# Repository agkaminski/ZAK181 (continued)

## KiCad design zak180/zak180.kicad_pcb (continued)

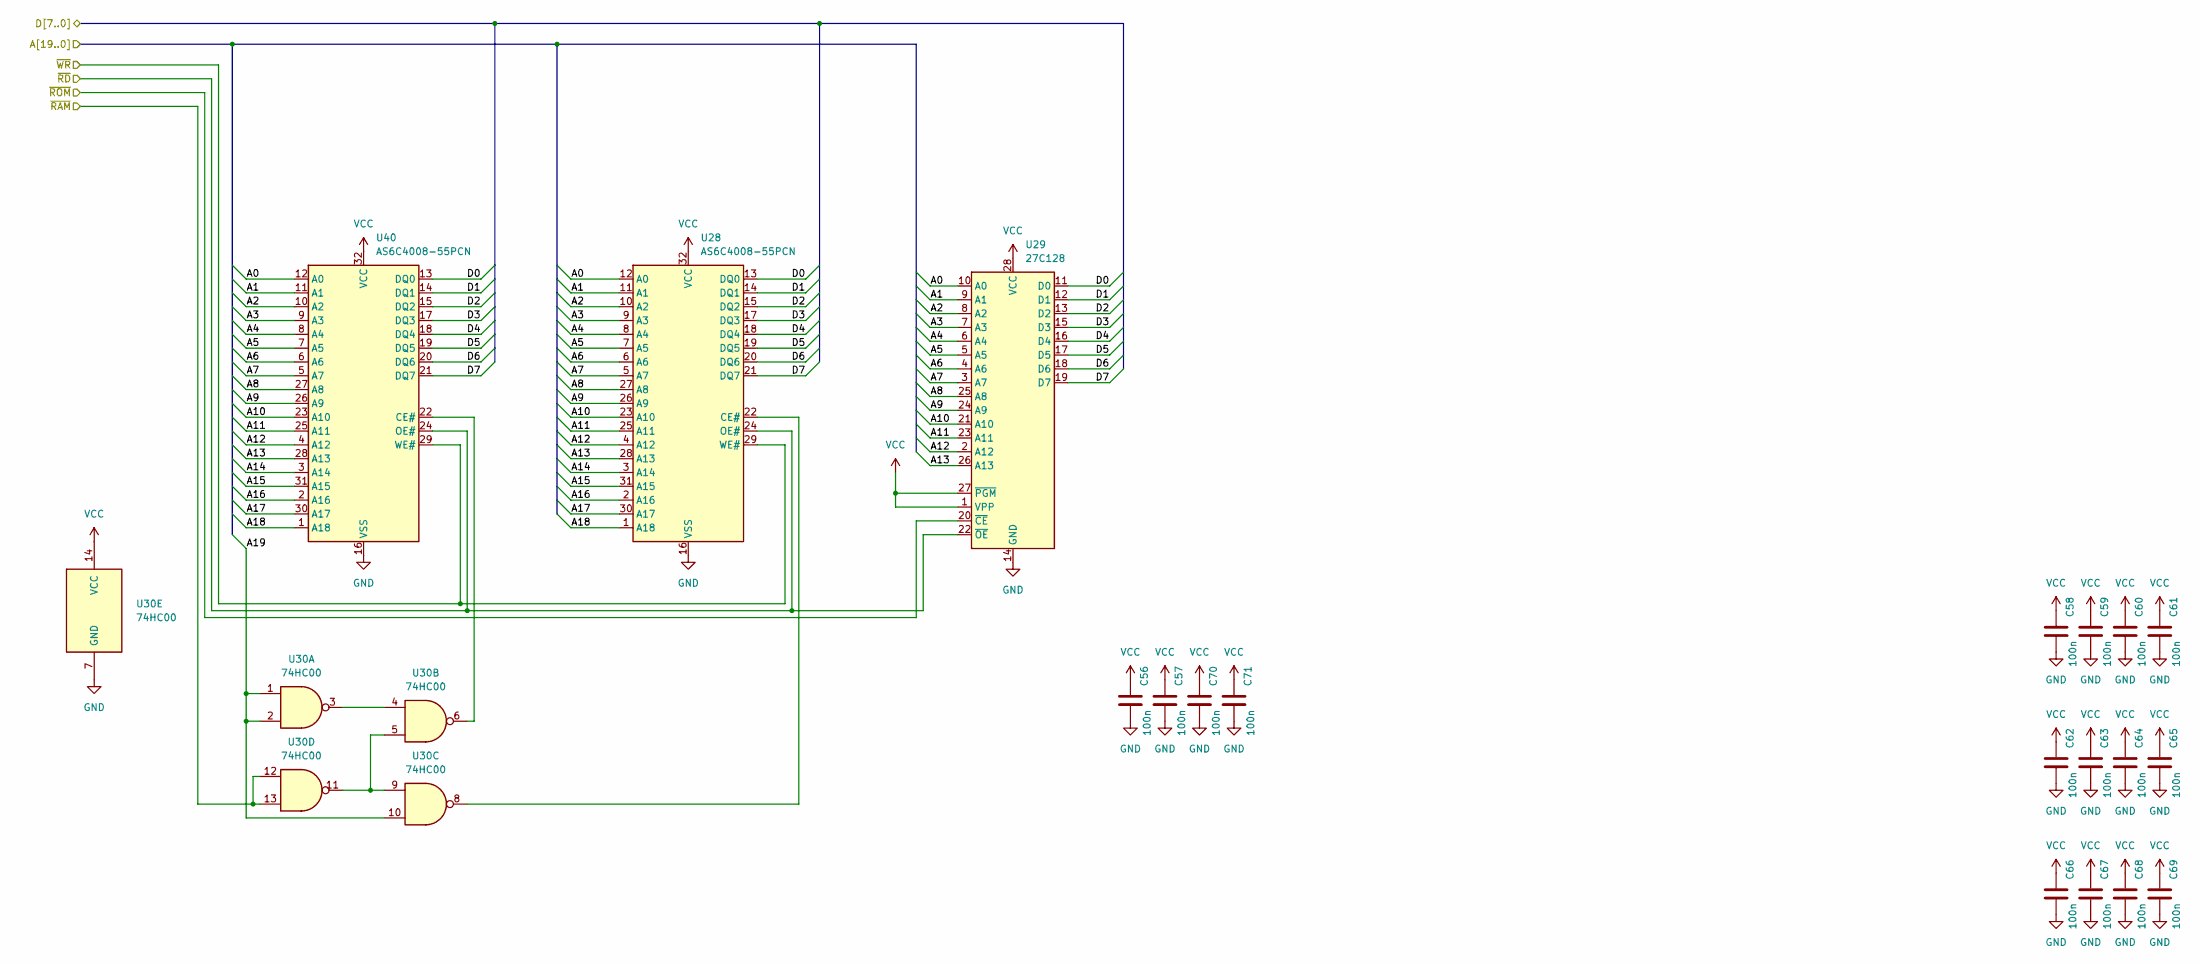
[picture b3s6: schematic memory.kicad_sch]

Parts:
C56, C57, C58, C59, C60, C61, C62, C63, C64, C65, C66, C67, C68, C69, C70, C71: 100n; C_Disc_D5.0mm_W2.5mm_P2.50mm
U28, U40: AS6C4008-55PCN; DIP-32_W15.24mm
U29: 27C128; DIP-28_W15.24mm
U30: 74HC00; DIP-14_W7.62mm

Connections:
/cpu/A0: U28.12 (A0), U29.10 (A0), U40.12 (A0); also elsewhere on the board
/cpu/A1: U28.11 (A1), U29.9 (A1), U40.11 (A1); also elsewhere on the board
/cpu/A2: U28.10 (A2), U29.8 (A2), U40.10 (A2); also elsewhere on the board
/cpu/A3: U28.9 (A3), U29.7 (A3), U40.9 (A3); also elsewhere on the board
/cpu/A4: U28.8 (A4), U29.6 (A4), U40.8 (A4); also elsewhere on the board
/cpu/A5: U28.7 (A5), U29.5 (A5), U40.7 (A5); also elsewhere on the board
/cpu/A6: U28.6 (A6), U29.4 (A6), U40.6 (A6); also elsewhere on the board
/cpu/A7: U28.5 (A7), U29.3 (A7), U40.5 (A7); also elsewhere on the board
/cpu/A8: U28.27 (A8), U29.25 (A8), U40.27 (A8); also elsewhere on the board
/cpu/A9: U28.26 (A9), U29.24 (A9), U40.26 (A9); also elsewhere on the board
/cpu/A10: U28.23 (A10), U29.21 (A10), U40.23 (A10); also elsewhere on the board
/cpu/A11: U28.25 (A11), U29.23 (A11), U40.25 (A11); also elsewhere on the board
/cpu/A12: U28.4 (A12), U29.2 (A12), U40.4 (A12); also elsewhere on the board
/cpu/A13: U28.28 (A13), U29.26 (A13), U40.28 (A13); also elsewhere on the board
/cpu/A14: U28.3 (A14), U40.3 (A14); also elsewhere on the board
/cpu/A15: U28.31 (A15), U40.31 (A15); also elsewhere on the board
/cpu/A16: U28.2 (A16), U40.2 (A16); also elsewhere on the board
/cpu/A17: U28.30 (A17), U40.30 (A17); also elsewhere on the board
/cpu/A18: U28.1 (A18), U40.1 (A18); also elsewhere on the board
/cpu/A19: U30.1, U30.2, U30.10; also elsewhere on the board
/cpu/D0: U28.13 (DQ0), U29.11 (D0), U40.13 (DQ0); also elsewhere on the board
/cpu/D1: U28.14 (DQ1), U29.12 (D1), U40.14 (DQ1); also elsewhere on the board
/cpu/D2: U28.15 (DQ2), U29.13 (D2), U40.15 (DQ2); also elsewhere on the board
/cpu/D3: U28.17 (DQ3), U29.15 (D3), U40.17 (DQ3); also elsewhere on the board
/cpu/D4: U28.18 (DQ4), U29.16 (D4), U40.18 (DQ4); also elsewhere on the board
/cpu/D5: U28.19 (DQ5), U29.17 (D5), U40.19 (DQ5); also elsewhere on the board
/cpu/D6: U28.20 (DQ6), U29.18 (D6), U40.20 (DQ6); also elsewhere on the board
/cpu/D7: U28.21 (DQ7), U29.19 (D7), U40.21 (DQ7); also elsewhere on the board
/cpu/~RAM: U30.12, U30.13; also elsewhere on the board
/cpu/~RD: U28.24 (OE#), U29.22 (~OE), U40.24 (OE#); also elsewhere on the board
/cpu/~ROM: U29.20 (~CE); also elsewhere on the board
/cpu/~WR: U28.29 (WE#), U40.29 (WE#); also elsewhere on the board
GND: C56.2, C57.2, C58.2, C59.2, C60.2, C61.2, C62.2, C63.2, C64.2, C65.2, C66.2, C67.2, C68.2, C69.2, C70.2, C71.2, U28.16 (VSS), U29.14 (GND), U30.7 (GND), U40.16 (VSS); also elsewhere on the board
unnamed: U28.22 (CE#), U30.8
unnamed: U30.3, U30.4
unnamed: U30.5, U30.9, U30.11
unnamed: U30.6, U40.22 (CE#)
VCC: C56.1, C57.1, C58.1, C59.1, C60.1, C61.1, C62.1, C63.1, C64.1, C65.1, C66.1, C67.1, C68.1, C69.1, C70.1, C71.1, U28.32 (VCC), U29.1 (VPP), U29.27 (~PGM), U29.28 (VCC), U30.14 (VCC), U40.32 (VCC); also elsewhere on the board

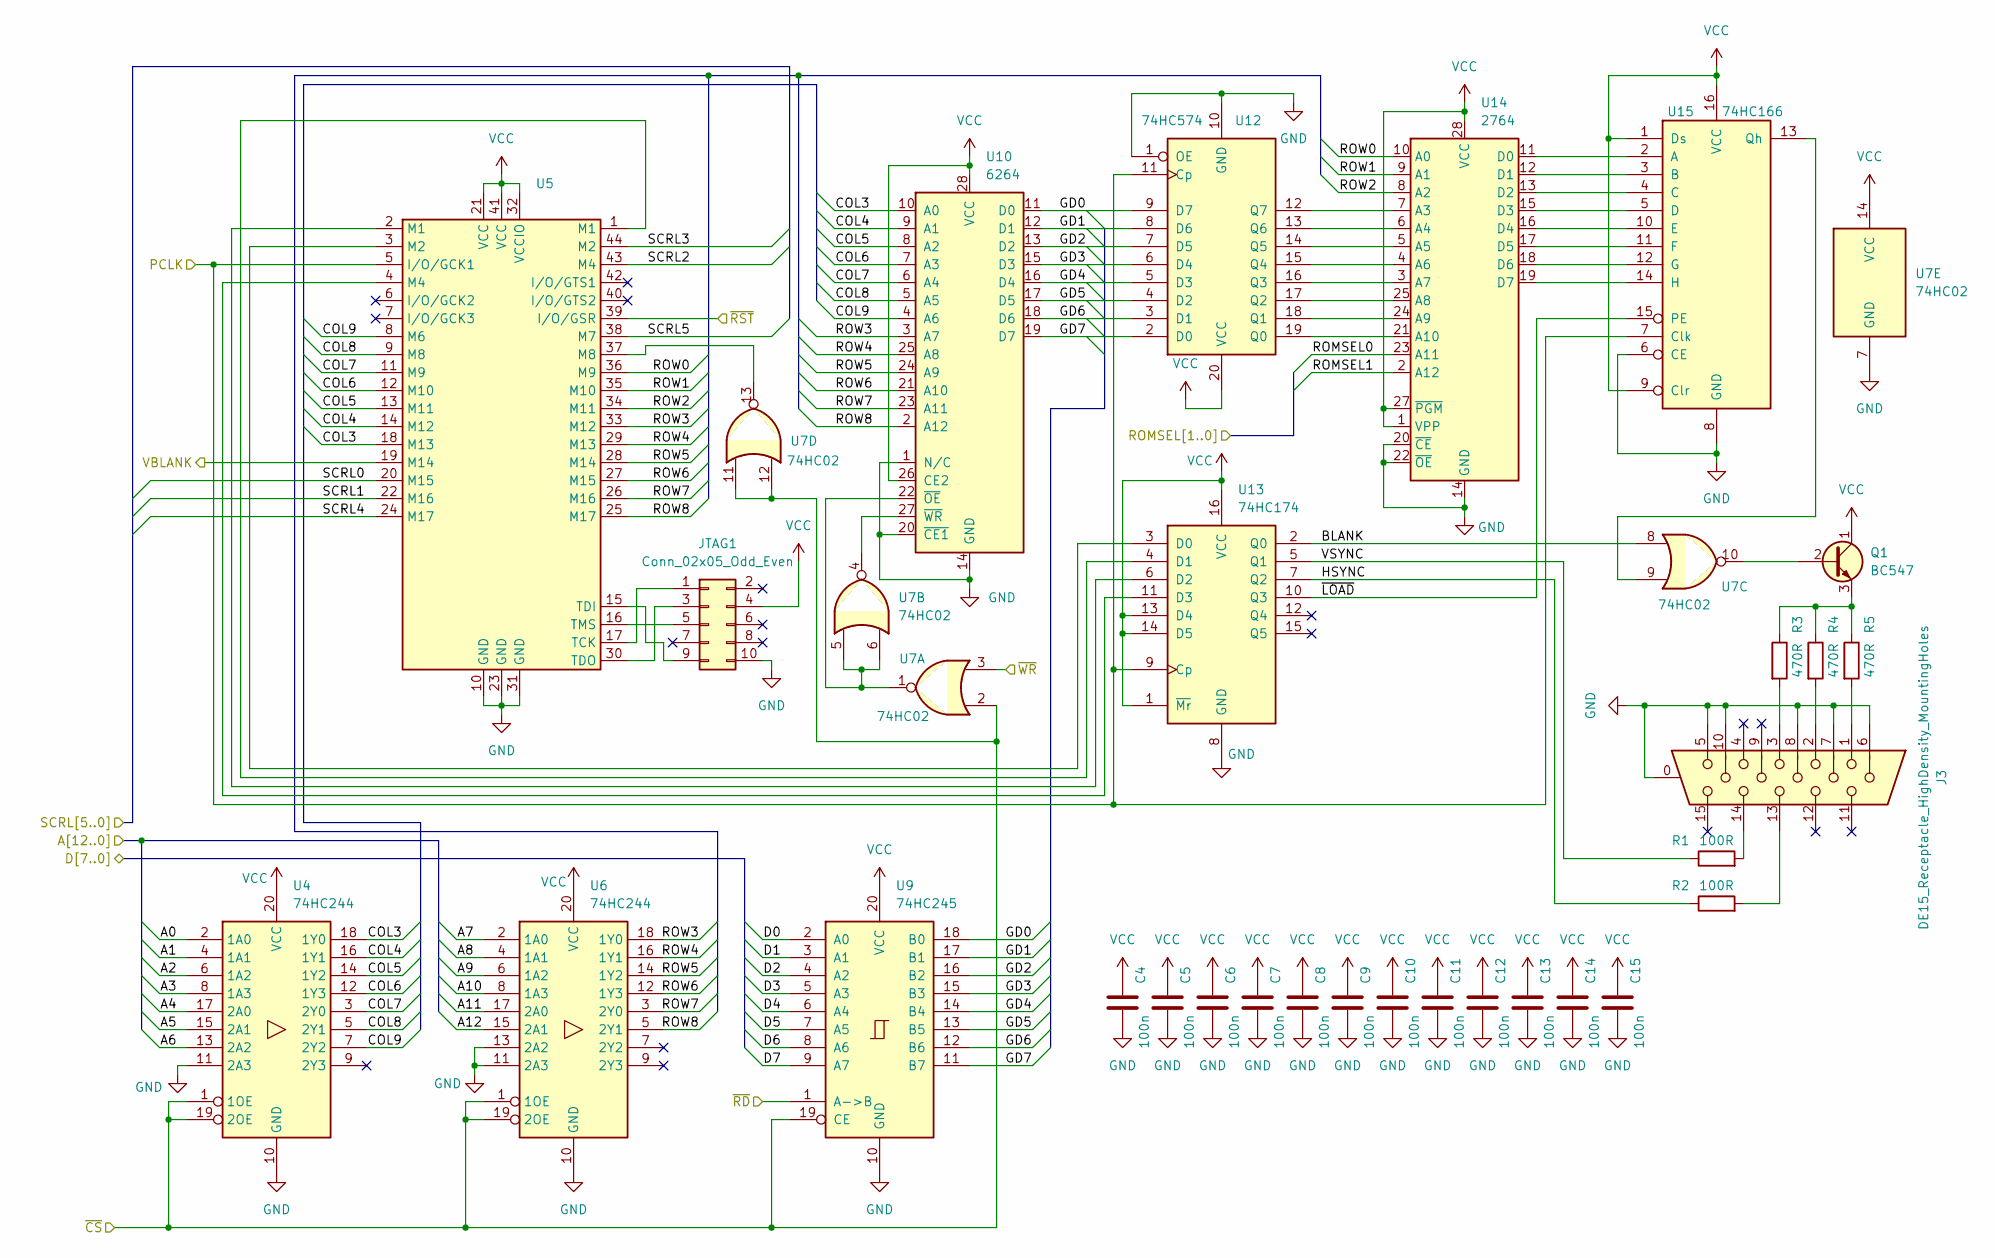
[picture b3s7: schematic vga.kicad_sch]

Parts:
C4, C5, C6, C7, C8, C9, C10, C11, C12, C13, C14, C15: 100n; C_Disc_D5.0mm_W2.5mm_P2.50mm
J3: DE15_Receptacle_HighDensity_MountingHoles; DSUB-15-HD_Female_Horizontal_P2.29x1.98mm_EdgePinOffset3.03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
JTAG1: Conn_02x05_Odd_Even; IDC-Header_2x05_P2.54mm_Vertical
Q1: BC547; TO-92
R1, R2: 100R; R_Axial_DIN0207_L6.3mm_D2.5mm_P7.62mm_Horizontal
R3, R4, R5: 470R; R_Axial_DIN0207_L6.3mm_D2.5mm_P7.62mm_Horizontal
U4: 74HC244; DIP-20_W7.62mm
U5: XC9536PC44; PLCC-44_THT-Socket
U6: 74HC244
U7: 74HC02; DIP-14_W7.62mm
U9: 74HC245; DIP-20_W7.62mm
U10: 6264; DIP-28_W15.24mm
U12: 74HC574; DIP-20_W7.62mm
U13: 74HC174; DIP-16_W7.62mm
U14: 2764; DIP-28_W15.24mm
U15: 74HC166; DIP-16_W7.62mm

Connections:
/clock/25.175 MHz: U5.5 (I/O/GCK1), U12.11 (Cp), U13.9 (Cp), U15.7 (Clk); also elsewhere on the board
/clock/~RST: U5.39 (I/O/GSR); also elsewhere on the board
/cpu/A0: U4.2 (1A0); also elsewhere on the board
/cpu/A1: U4.4 (1A1); also elsewhere on the board
/cpu/A2: U4.6 (1A2); also elsewhere on the board
/cpu/A3: U4.8 (1A3); also elsewhere on the board
/cpu/A4: U4.17 (2A0); also elsewhere on the board
/cpu/A5: U4.15 (2A1); also elsewhere on the board
/cpu/A6: U4.13 (2A2); also elsewhere on the board
/cpu/A7: U6.2 (1A0); also elsewhere on the board
/cpu/A8: U6.4 (1A1); also elsewhere on the board
/cpu/A9: U6.6 (1A2); also elsewhere on the board
/cpu/A10: U6.8 (1A3); also elsewhere on the board
/cpu/A11: U6.17 (2A0); also elsewhere on the board
/cpu/A12: U6.15 (2A1); also elsewhere on the board
/cpu/D0: U9.2 (A0); also elsewhere on the board
/cpu/D1: U9.3 (A1); also elsewhere on the board
/cpu/D2: U9.4 (A2); also elsewhere on the board
/cpu/D3: U9.5 (A3); also elsewhere on the board
/cpu/D4: U9.6 (A4); also elsewhere on the board
/cpu/D5: U9.7 (A5); also elsewhere on the board
/cpu/D6: U9.8 (A6); also elsewhere on the board
/cpu/D7: U9.9 (A7); also elsewhere on the board
/cpu/VBLANK: U5.19 (M14); also elsewhere on the board
/cpu/~RD: U9.1 (A->B); also elsewhere on the board
/cpu/~VRAM: U4.1 (1OE), U4.19 (2OE), U6.1 (1OE), U6.19 (2OE), U7.2, U7.11, U7.12, U9.19 (CE); also elsewhere on the board
/cpu/~WR: U7.3; also elsewhere on the board
/sound/ROMSEL0: U14.23 (A11); also elsewhere on the board
/sound/ROMSEL1: U14.2 (A12); also elsewhere on the board
/sound/SCRL0: U5.20 (M15); also elsewhere on the board
/sound/SCRL1: U5.22 (M16); also elsewhere on the board
/sound/SCRL2: U5.43 (M4); also elsewhere on the board
/sound/SCRL3: U5.44 (M2); also elsewhere on the board
/sound/SCRL4: U5.24 (M17); also elsewhere on the board
/sound/SCRL5: U5.38 (M7); also elsewhere on the board
/vga/BLANK: U7.8, U13.2 (Q0)
/vga/COL3: U4.18 (1Y0), U5.18 (M13), U10.10 (A0)
/vga/COL4: U4.16 (1Y1), U5.14 (M12), U10.9 (A1)
/vga/COL5: U4.14 (1Y2), U5.13 (M11), U10.8 (A2)
/vga/COL6: U4.12 (1Y3), U5.12 (M10), U10.7 (A3)
/vga/COL7: U4.3 (2Y0), U5.11 (M9), U10.6 (A4)
/vga/COL8: U4.5 (2Y1), U5.9 (M8), U10.5 (A5)
/vga/COL9: U4.7 (2Y2), U5.8 (M6), U10.4 (A6)
/vga/GD0: U9.18 (B0), U10.11 (D0), U12.9 (D7)
/vga/GD1: U9.17 (B1), U10.12 (D1), U12.8 (D6)
/vga/GD2: U9.16 (B2), U10.13 (D2), U12.7 (D5)
/vga/GD3: U9.15 (B3), U10.15 (D3), U12.6 (D4)
/vga/GD4: U9.14 (B4), U10.16 (D4), U12.5 (D3)
/vga/GD5: U9.13 (B5), U10.17 (D5), U12.4 (D2)
/vga/GD6: U9.12 (B6), U10.18 (D6), U12.3 (D1)
/vga/GD7: U9.11 (B7), U10.19 (D7), U12.2 (D0)
/vga/HSYNC: R2.1, U13.7 (Q2)
/vga/ROW0: U5.36 (M9), U14.10 (A0)
/vga/ROW1: U5.35 (M10), U14.9 (A1)
/vga/ROW2: U5.34 (M11), U14.8 (A2)
/vga/ROW3: U5.33 (M12), U6.18 (1Y0), U10.3 (A7)
/vga/ROW4: U5.29 (M13), U6.16 (1Y1), U10.25 (A8)
/vga/ROW5: U5.28 (M14), U6.14 (1Y2), U10.24 (A9)
/vga/ROW6: U5.27 (M15), U6.12 (1Y3), U10.21 (A10)
/vga/ROW7: U5.26 (M16), U6.3 (2Y0), U10.23 (A11)
/vga/ROW8: U5.25 (M17), U6.5 (2Y1), U10.2 (A12)
/vga/VSYNC: R1.1, U13.5 (Q1)
/vga/~LOAD: U13.10 (Q3), U15.15 (PE)
GND: C4.2, C5.2, C6.2, C7.2, C8.2, C9.2, C10.2, C11.2, C12.2, C13.2, C14.2, C15.2, J3.0, J3.5, J3.6, J3.7, J3.8, J3.10, JTAG1.10, U4.10 (GND), U4.11 (2A3), U5.10 (GND), U5.23 (GND), U5.31 (GND), U6.10 (GND), U6.11 (2A3), U6.13 (2A2), U7.7 (GND), U9.10 (GND), U10.1 (N/C), U10.14 (GND), U10.20 (~CE1), U12.1 (OE), U12.10 (GND), U13.8 (GND), U14.14 (GND), U14.20 (~CE), U14.22 (~OE), U15.6 (CE), U15.8 (GND); also elsewhere on the board
unnamed: J3.1, R5.2
unnamed: J3.2, R4.2
unnamed: J3.3, R3.2
unnamed: J3.13, R2.2
unnamed: J3.14, R1.2
unnamed: JTAG1.1, U5.17 (TCK)
unnamed: JTAG1.3, U5.30 (TDO)
unnamed: JTAG1.5, U5.16 (TMS)
unnamed: JTAG1.9, U5.15 (TDI)
unnamed: Q1.2 (B), U7.10
unnamed: Q1.3 (E), R3.1, R4.1, R5.1
unnamed: U5.37 (M8), U7.13
unnamed: U7.1, U7.5, U7.6, U10.22 (~OE)
unnamed: U7.4, U10.27 (~WR)
unnamed: U12.19 (Q0), U14.21 (A10)
unnamed: U12.18 (Q1), U14.24 (A9)
unnamed: U12.17 (Q2), U14.25 (A8)
unnamed: U12.16 (Q3), U14.3 (A7)
unnamed: U12.15 (Q4), U14.4 (A6)
unnamed: U12.14 (Q5), U14.5 (A5)
unnamed: U12.13 (Q6), U14.6 (A4)
unnamed: U12.12 (Q7), U14.7 (A3)
unnamed: U5.3 (M2), U13.3 (D0)
unnamed: U5.1 (M1), U13.4 (D1)
unnamed: U5.2 (M1), U13.6 (D2)
unnamed: U5.4 (M4), U13.11 (D3)
unnamed: U14.11 (D0), U15.2 (A)
unnamed: U14.12 (D1), U15.3 (B)
unnamed: U14.13 (D2), U15.4 (C)
unnamed: U14.15 (D3), U15.5 (D)
unnamed: U14.16 (D4), U15.10 (E)
unnamed: U14.17 (D5), U15.11 (F)
unnamed: U14.18 (D6), U15.12 (G)
unnamed: U14.19 (D7), U15.14 (H)
unnamed: U7.9, U15.13 (Qh)
VCC: C4.1, C5.1, C6.1, C7.1, C8.1, C9.1, C10.1, C11.1, C12.1, C13.1, C14.1, C15.1, JTAG1.4, Q1.1 (C), U4.20 (VCC), U5.21 (VCC), U5.32 (VCCIO), U5.41 (VCC), U6.20 (VCC), U7.14 (VCC), U9.20 (VCC), U10.26 (CE2), U10.28 (VCC), U12.20 (VCC), U13.1 (~Mr), U13.13 (D4), U13.14 (D5), U13.16 (VCC), U14.1 (VPP), U14.27 (~PGM), U14.28 (VCC), U15.1 (Ds), U15.9 (Clr), U15.16 (VCC); also elsewhere on the board

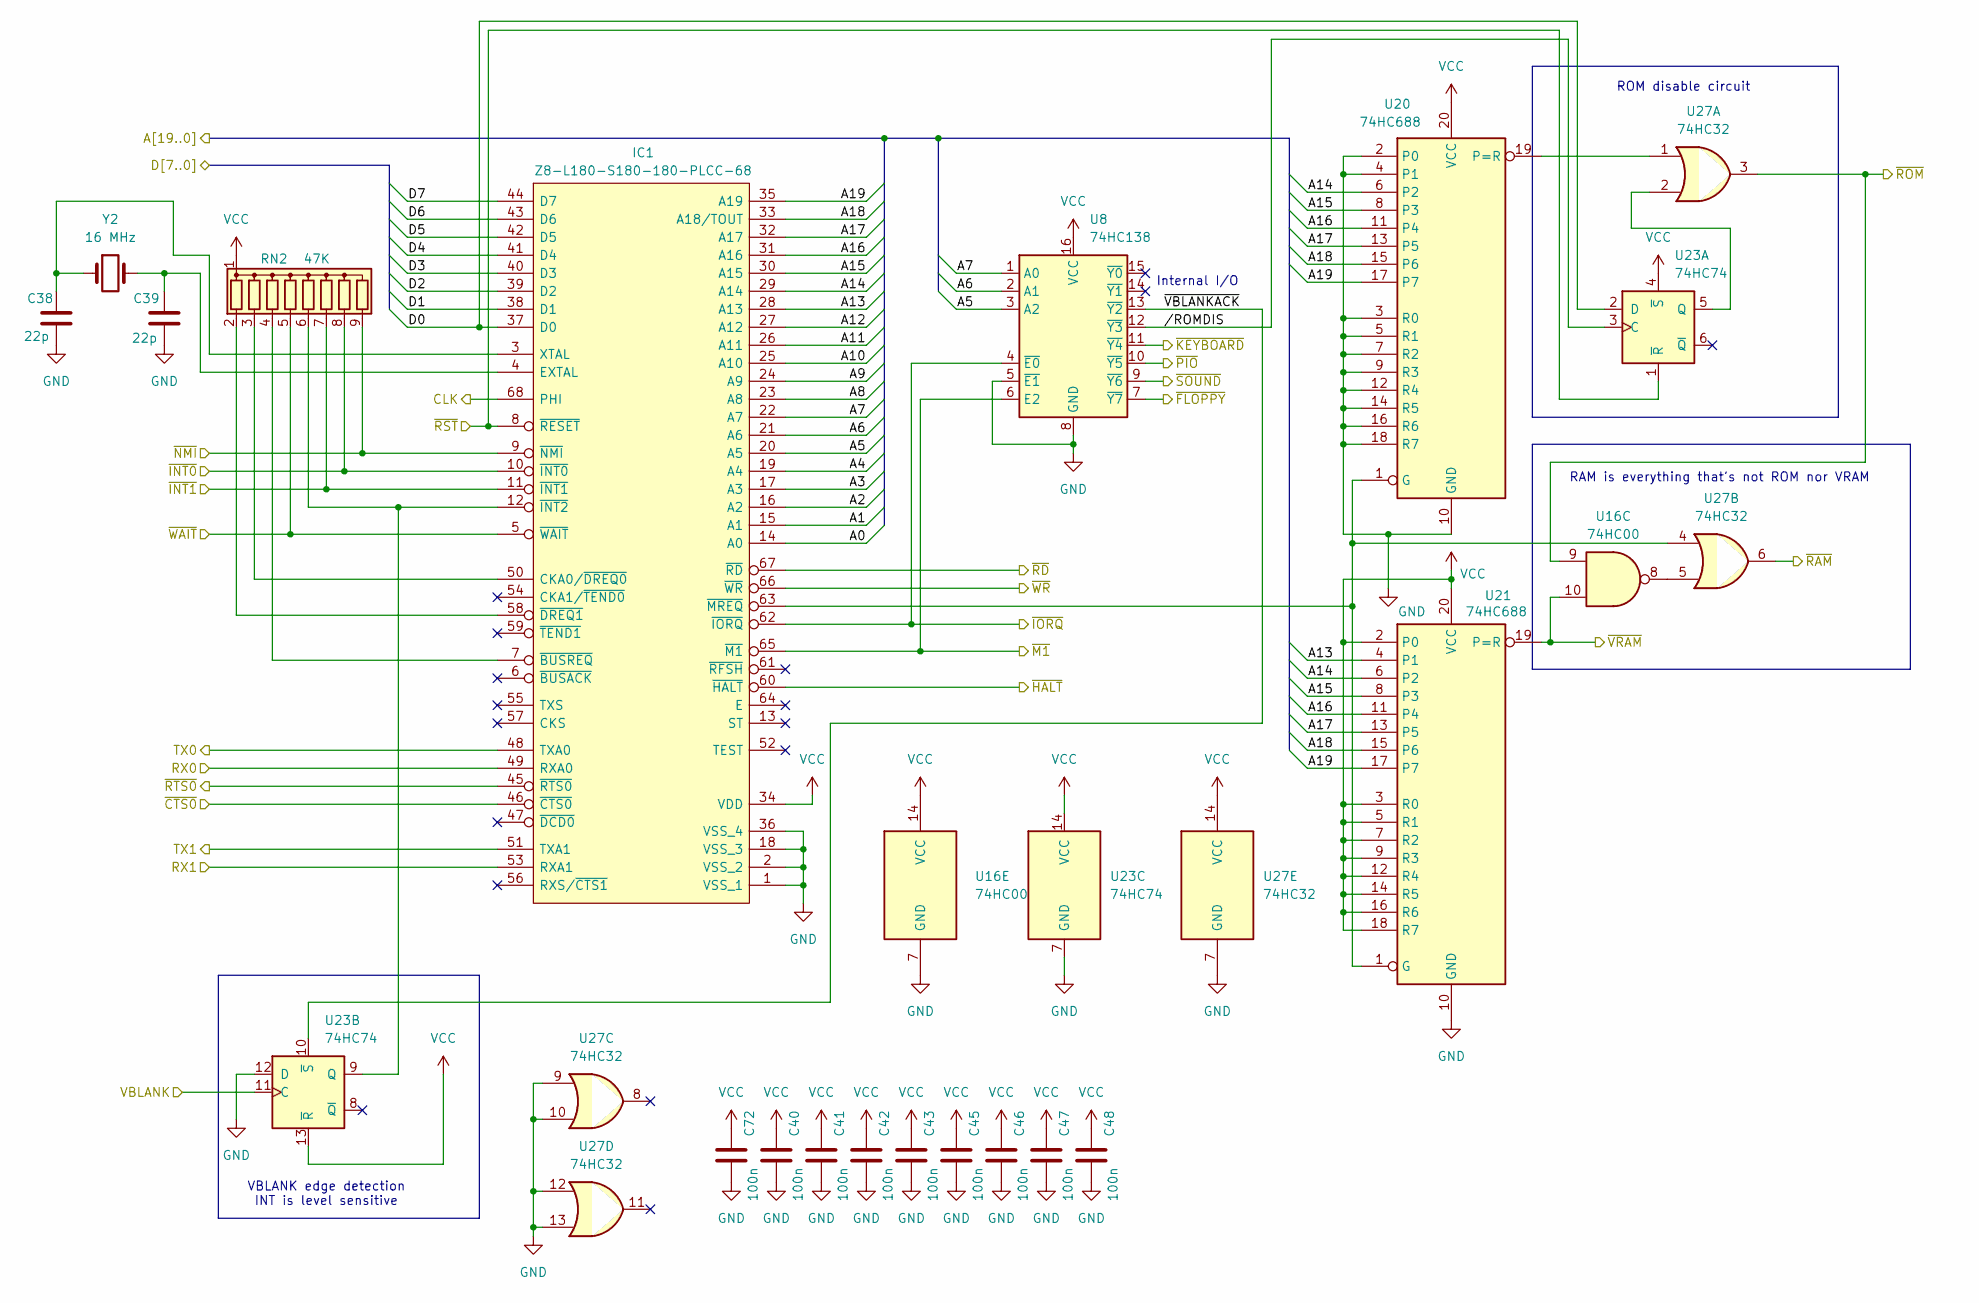
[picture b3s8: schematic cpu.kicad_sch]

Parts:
C38, C39: 22p; C_Disc_D4.3mm_W1.9mm_P5.00mm
C40, C41, C42, C43, C45, C46, C47, C48, C72: 100n; C_Disc_D5.0mm_W2.5mm_P2.50mm
IC1: Z8-L180-S180-180-PLCC-68; PLCC-68_THT-Socket; Manufacturer_Part_Number Z8S18033VSG; Mouser Part Number 692-Z8S18033VSG
RN2: 47K; R_Array_SIP9
U8: 74HC138; DIP-16_W7.62mm
U16: 74HC00; DIP-14_W7.62mm
U20, U21: 74HC688; DIP-20_W7.62mm
U23: 74HC74; DIP-14_W7.62mm
U27: 74HC32; DIP-14_W7.62mm
Y2: 16 MHz; Crystal_HC49-4H_Vertical

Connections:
/clock/~RST: IC1.8 (~RESET), U23.1 (~R); also elsewhere on the board
/cpu/A0: IC1.14 (A0); also elsewhere on the board
/cpu/A1: IC1.15 (A1); also elsewhere on the board
/cpu/A2: IC1.16 (A2); also elsewhere on the board
/cpu/A3: IC1.17 (A3); also elsewhere on the board
/cpu/A4: IC1.19 (A4); also elsewhere on the board
/cpu/A5: IC1.20 (A5), U8.3 (A2); also elsewhere on the board
/cpu/A6: IC1.21 (A6), U8.2 (A1); also elsewhere on the board
/cpu/A7: IC1.22 (A7), U8.1 (A0); also elsewhere on the board
/cpu/A8: IC1.23 (A8); also elsewhere on the board
/cpu/A9: IC1.24 (A9); also elsewhere on the board
/cpu/A10: IC1.25 (A10); also elsewhere on the board
/cpu/A11: IC1.26 (A11); also elsewhere on the board
/cpu/A12: IC1.27 (A12); also elsewhere on the board
/cpu/A13: IC1.28 (A13), U21.4 (P1); also elsewhere on the board
/cpu/A14: IC1.29 (A14), U20.6 (P2), U21.6 (P2); also elsewhere on the board
/cpu/A15: IC1.30 (A15), U20.8 (P3), U21.8 (P3); also elsewhere on the board
/cpu/A16: IC1.31 (A16), U20.11 (P4), U21.11 (P4); also elsewhere on the board
/cpu/A17: IC1.32 (A17), U20.13 (P5), U21.13 (P5); also elsewhere on the board
/cpu/A18: IC1.33 (A18/TOUT), U20.15 (P6), U21.15 (P6); also elsewhere on the board
/cpu/A19: IC1.35 (A19), U20.17 (P7), U21.17 (P7); also elsewhere on the board
/cpu/CLK: IC1.68 (PHI); also elsewhere on the board
/cpu/D0: IC1.37 (D0), U23.2 (D); also elsewhere on the board
/cpu/D1: IC1.38 (D1); also elsewhere on the board
/cpu/D2: IC1.39 (D2); also elsewhere on the board
/cpu/D3: IC1.40 (D3); also elsewhere on the board
/cpu/D4: IC1.41 (D4); also elsewhere on the board
/cpu/D5: IC1.42 (D5); also elsewhere on the board
/cpu/D6: IC1.43 (D6); also elsewhere on the board
/cpu/D7: IC1.44 (D7); also elsewhere on the board
/cpu/RX0: IC1.49 (RXA0); also elsewhere on the board
/cpu/RX1: IC1.53 (RXA1); also elsewhere on the board
/cpu/TX0: IC1.48 (TXA0); also elsewhere on the board
/cpu/TX1: IC1.51 (TXA1); also elsewhere on the board
/cpu/VBLANK: U23.11 (C); also elsewhere on the board
/cpu//ROMDIS: U8.12 (~Y3), U23.3 (C)
/cpu/~CTS0: IC1.46 (~CTS0); also elsewhere on the board
/cpu/~FLOPPY: U8.7 (~Y7); also elsewhere on the board
/cpu/~HALT: IC1.60 (~HALT); also elsewhere on the board
/cpu/~INT0: IC1.10 (~INT0), RN2.8 (R7); also elsewhere on the board
/cpu/~INT1: IC1.11 (~INT1), RN2.7 (R6); also elsewhere on the board
/cpu/~IORQ: IC1.62 (~IORQ), U8.4 (~E0); also elsewhere on the board
/cpu/~KEYBOARD: U8.11 (~Y4); also elsewhere on the board
/cpu/~M1: IC1.65 (~M1), U8.6 (E2); also elsewhere on the board
/cpu/~NMI: IC1.9 (~NMI), RN2.9 (R8)
/cpu/~PIO: U8.10 (~Y5); also elsewhere on the board
/cpu/~RAM: U27.6; also elsewhere on the board
/cpu/~RD: IC1.67 (~RD); also elsewhere on the board
/cpu/~ROM: U16.9, U27.3; also elsewhere on the board
/cpu/~RTS0: IC1.45 (~RTS0); also elsewhere on the board
/cpu/~SOUND: U8.9 (~Y6); also elsewhere on the board
/cpu/~VBLANKACK: U8.13 (~Y2), U23.10 (~S)
/cpu/~VRAM: U16.10, U21.19 (P=R); also elsewhere on the board
/cpu/~WAIT: IC1.5 (~WAIT), RN2.5 (R4)
/cpu/~WR: IC1.66 (~WR); also elsewhere on the board
GND: C38.1, C39.1, C40.2, C41.2, C42.2, C43.2, C45.2, C46.2, C47.2, C48.2, C72.2, IC1.1 (VSS_1), IC1.2 (VSS_2), IC1.18 (VSS_3), IC1.36 (VSS_4), U8.5 (~E1), U8.8 (GND), U16.7 (GND), U20.2 (P0), U20.3 (R0), U20.4 (P1), U20.5 (R1), U20.7 (R2), U20.9 (R3), U20.10 (GND), U20.12 (R4), U20.14 (R5), U20.16 (R6), U20.18 (R7), U21.10 (GND), U23.7 (GND), U23.12 (D), U27.7 (GND), U27.9, U27.10, U27.12, U27.13; also elsewhere on the board
unnamed: IC1.50 (CKA0/~DREQ0), RN2.3 (R2)
unnamed: C39.2, IC1.4 (EXTAL), Y2.2
unnamed: C38.2, IC1.3 (XTAL), Y2.1
unnamed: IC1.7 (~BUSREQ), RN2.4 (R3)
unnamed: IC1.58 (~DREQ1), RN2.2 (R1)
unnamed: IC1.12 (~INT2), RN2.6 (R5), U23.9 (Q)
unnamed: IC1.63 (~MREQ), U20.1 (G), U21.1 (G), U27.4
unnamed: U16.8, U27.5
unnamed: U20.19 (P=R), U27.1
unnamed: U23.5 (Q), U27.2
VCC: C40.1, C41.1, C42.1, C43.1, C45.1, C46.1, C47.1, C48.1, C72.1, IC1.34 (VDD), RN2.1 (common), U8.16 (VCC), U16.14 (VCC), U20.20 (VCC), U21.2 (P0), U21.3 (R0), U21.5 (R1), U21.7 (R2), U21.9 (R3), U21.12 (R4), U21.14 (R5), U21.16 (R6), U21.18 (R7), U21.20 (VCC), U23.4 (~S), U23.13 (~R), U23.14 (VCC), U27.14 (VCC); also elsewhere on the board

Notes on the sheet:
RAM is everything that's not ROM nor VRAM
Internal I/O
ROM disable circuit
VBLANK edge detection INT is level sensitive

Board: 2 copper layers, 163 parts (0 on the bottom side), 250 nets, no tracks yet.

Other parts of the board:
C44, C52, C53: 100n; C_Disc_D5.0mm_W2.5mm_P2.50mm
C49, C50, C51: 10u; CP_Radial_D5.0mm_P2.50mm
C54, C55: 470u; CP_Radial_D10.0mm_P5.00mm
J5: Conn_02x06_Odd_Even; IDC-Header_2x06_P2.54mm_Vertical
J7: DE9_Plug_MountingHoles; DSUB-9_Male_Horizontal_P2.77x2.84mm_EdgePinOffset7.70mm_Hou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
J8: USB_C_Receptacle_USB2.0_14P; USB_C_Receptacle_G-Switch_GT-USB-7010ASV
R34, R35: 1K5; R_Axial_DIN0207_L6.3mm_D2.5mm_P7.62mm_Horizontal
U22: 74HC244; DIP-20_W7.62mm
U25: MAX232; DIP-16_W7.62mm
U26: CH340N; SOP-8_3.9x4.9mm_P1.27mm

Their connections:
/cpu/A0: U22.18 (1Y0); also elsewhere on the board
/cpu/A1: U22.16 (1Y1); also elsewhere on the board
/cpu/A2: U22.14 (1Y2); also elsewhere on the board
/cpu/A3: U22.12 (1Y3); also elsewhere on the board
/cpu/A4: U22.3 (2Y0); also elsewhere on the board
/cpu/D0: J5.5; also elsewhere on the board
/cpu/D1: J5.7; also elsewhere on the board
/cpu/D2: J5.9; also elsewhere on the board
/cpu/D3: J5.11; also elsewhere on the board
/cpu/RX0: U25.12 (R1OUT); also elsewhere on the board
/cpu/RX1: U26.7 (RXD); also elsewhere on the board
/cpu/TX0: U25.11 (T1IN); also elsewhere on the board
/cpu/TX1: U26.6 (TXD); also elsewhere on the board
/cpu/~CTS0: U25.9 (R2OUT); also elsewhere on the board
/cpu/~KEYBOARD: J5.3, U22.1 (1OE), U22.19 (2OE); also elsewhere on the board
/cpu/~RTS0: U25.10 (T2IN); also elsewhere on the board
GND: C44.2, C52.2, C53.2, C54.2, C55.2, J5.2, J7.0 (PAD), J7.5, J8.A1 (GND), J8.A12 (GND), J8.B1 (GND), J8.B12 (GND), J8.S1 (SHIELD), R34.2, R35.2, U22.10 (GND), U22.11 (2A3), U22.13 (2A2), U22.15 (2A1), U25.15 (GND), U26.3 (GND); also elsewhere on the board
unnamed: J5.4, U22.2 (1A0)
unnamed: J5.6, U22.4 (1A1)
unnamed: J5.8, U22.6 (1A2)
unnamed: J5.10, U22.8 (1A3)
unnamed: J5.12, U22.17 (2A0)
unnamed: J8.A5 (CC1), R35.1
unnamed: J8.B5 (CC2), R34.1
unnamed: C51.1, U25.1 (C1+)
unnamed: C51.2, U25.3 (C1-)
unnamed: C49.1, U25.4 (C2+)
unnamed: C49.2, U25.5 (C2-)
unnamed: J7.2, U25.13 (R1IN)
unnamed: J7.8, U25.8 (R2IN)
unnamed: J7.3, U25.14 (T1OUT)
unnamed: J7.7, U25.7 (T2OUT)
unnamed: C50.1, U25.2 (VS+)
unnamed: C50.2, U25.6 (VS-)
unnamed: J8.A6 (D+), J8.B6 (D+), U26.1 (UD+)
unnamed: J8.A7 (D-), J8.B7 (D-), U26.2 (UD-)
unnamed: C52.1, U26.8 (V3)
VCC: C44.1, C53.1, C54.1, C55.1, J5.1, J8.A4 (VBUS), J8.A9 (VBUS), J8.B4 (VBUS), J8.B9 (VBUS), U22.20 (VCC), U25.16 (VCC), U26.5 (VCC); also elsewhere on the board

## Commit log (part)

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2024-08-18 HW: Floppy, VGA, PIO and sound
2024-08-19 Import VGA CPLD stuff
2024-08-19 HW: Further work on schematic
2024-08-19 Add some datasheets
2024-08-20 HW: Before abandoning DRAM
2024-08-20 HW: Change RAM to static
2024-08-20 HW: PCB complete
2024-08-20 HW: PCB finishing touches
2024-08-20 HW: Fix RST line
2024-08-20 HW: Revision A
2025-02-12 Add README and LICENSE
2025-02-12 Update README and issues
2025-02-12 FW: Add simple dead/alive test (crasm)
2025-02-12 FW: start work on drivers
2025-02-12 HW: Fix UART1 having RX and TX swapped
2025-02-12 Bootloader: start work on bootstrap
2025-02-12 driver/floppy: Fix write regression
2025-02-12 Update schematic pdf file
2025-02-12 bootloader: Working kernel load
2025-02-12 Add devkit STL model
2025-02-12 Add memory maps to README
2025-02-12 driver/floppy: fix buggy retval check
2025-02-12 floppy: Fix disk change detection
2025-02-12 HW: update schematic pdf
2025-02-12 VGA: working VGA
2025-02-12 HW: remove unnecessary kicad files
2025-02-12 driver/floppy: add comment about not working eject detection, change delay
2025-02-12 Kernel: Initial memory management
2025-02-12 driver/floppy: remove redundant seek
2025-02-12 FAT12: start work on open
2025-02-12 vga: mostly working vga driver
2025-02-12 FAT12: Simplify file_write
2025-02-12 FAT12: optimize sector re-access, update FAT copy on write
2025-02-12 UART: use interrupts
2025-02-12 Remove redundant file
2025-02-12 bootloader: Working bootstrap to high RAM
2025-02-12 driver/floppy: Working read and write
2025-02-12 Drivers: Add makefile, fix AY-3-8912
2025-02-12 driver: Start work on floppy controller driver
2025-02-12 FAT12: Working file open and read
2025-02-12 driver/floppy: add floppy interface wrapers
2025-02-12 FAT12: start work on truncate
2025-02-12 FAT12: Fix UB in file_read preventing reads over 512 bytes
2025-02-12 driver: start work on VGA
2025-02-12 FW: Add interrupts handling in bootloader
2025-02-12 Bootloader: relocate bootloader to common 1 to make bank area coherently scratchpad
2025-02-12 driver/floppy: slight cleanup
2025-02-12 driver/floppy: improve error handling
2025-02-12 Kernel: Working linear memory alloc/free
2025-02-12 filesystem: Working FAT entry getter
2025-02-12 driver/floppy: Fix build, use asm local labels
2025-02-12 FW: Enable SDCC optimizations
2025-02-12 HW: Fix bug in I/O decoder
2025-02-12 FAT12: Separate read file and dir, use errno
2025-02-12 kernel/memory: working split/merge
2025-02-12 driver: add PIO driver
2025-02-12 driver/floppy: Rename lower layer, working access to the whole disk
2025-02-12 driver/floppy: refactor
2025-02-12 FAT12: working file write
2025-02-12 VGA: put vga_set in critical section
2025-02-12 UART: Fix warning
2025-02-12 VGA: remove dead variables
2025-02-12 VGA: new approach - double buffered partial refresh
2025-02-12 driver/floppy: optimize FIFO read/write, add timeout
2025-02-12 HW: Fix address and data buses being swapped for keyboard connector
2025-02-12 driver/floppy: remove explicit RET
2025-02-12 HW: revision C
2025-02-12 FAT: start work on a'la vfs FAT implementation (WIP)
2025-02-12 VGA: handle tab
2025-02-12 kernel: save/restore MMU context
2025-02-12 blk: fix sync size type in API
2025-02-12 vfs: start vfs API implementation (WIP)
2025-02-12 HW: remove rev A gerbers
2025-02-12 kernel/memory: remove debug
2025-02-12 kernel: define block device API + floopy blk
2025-02-12 driver: compile all drivers to the single lib
2025-02-12 kernel: working scheduler
2025-02-12 HW: Fix unconnected /SOUND net, add /RST header and /DTR power supply
2025-02-12 VGA: guard against cursor handling in the interrupt
2025-02-12 test: optimize kmalloc test
2025-02-12 kernel: working thread sleep
2025-02-12 kernel: change code structure
2025-02-12 Replace irq disable with scheduler lock. Make critical section not enabled on boot
2025-02-12 kernel: start work on FS abstraction
2025-02-12 fw: move list to lib
2025-02-12 memory: import kmalloc
2025-02-12 vfs: partial fs API implementation
2025-02-12 kernel/proc: fix incorrect version of timer_get being used
2025-02-12 kernel: start work on threads
2025-02-12 kernel: working systick timer
2025-02-12 fw: fix header paths
2025-02-12 kernel: remove redundant file
2025-02-12 kernel: add kmalloc and condwait tests
2025-02-12 fs: extract vfs lookup from fs_open
2025-02-12 fs: use blk interface in FAT, remove adhoc one. Build fix
2025-02-12 proc: fix timeout on cond
2025-02-12 dev: fix floppy pseud-cache thining it has read sector #0
2025-02-12 lib/id: exclude 0 from being valid id
2025-02-12 lib: add simple id allocator/structure
2025-02-12 kernel: "compress" crt0.s to save 512 CODE bytes
2025-02-12 proc: fix temp scratch mappings not restoring previous mapping
2025-02-12 kernel: fix makefile clean
2025-02-12 3D: fix bottom no longer matching case, move it to the one FreeCAD file
2025-02-12 vga: fix artifacts when accessing FDD due to the late IRQ
2025-02-12 kernel: mount rootfs
2025-02-12 kernel: change ktime_t to signed type
2025-02-12 fs: remove dentry from file node, add FAT cache
2025-02-12 fs: working fs_truncate and fs_write. Add FAT set grouping
2025-02-12 mem: make init verbose
2025-02-12 kernel: add syscall implementation
2025-02-12 dev: fix floppy blk argument types
2025-02-12 proc: add assertions
2025-02-12 fat: remove dead code
2025-02-12 fs: change readdir API - don't increment idx internally
2025-02-12 3D/case: add vent holes, move PCB to clear IO plugs
2025-02-12 proc: remove initial thread id allocator
2025-02-12 vfs: finish basic vfs API
2025-02-12 fs: init locks (not strictly needed when lock is zeroed-out)
2025-02-12 fs: semi-working fs_open
2025-02-12 fat: remove cluster/offset caching - not needed due to FAT caching
2025-02-12 kernel: fix typo
2025-02-12 3d: add keyboard support bar model
2025-02-12 proc: replace not working sleeping list with bheap
2025-02-12 fs: implement fs_remove and fat_op_remove
2025-02-12 kmalloc: revert payload alignment change
2025-02-12 fat: refactor truncate to generalise FAT chain trimming
    Fix bugs:
    - truncate in some cases hasn't been zeroing whole space,
    - fat_sync did nothing
2025-02-12 proc: add cond var
2025-02-12 proc: fix thread_yield hogging interrupts
2025-02-12 lib: move list from macros to functions, save ~1 KB of code size
2025-02-12 fs: working fs_readdir
2025-02-12 fs/fat: optimise FA12_SECTOR_SIZE operations for code size
2025-02-12 proc: WIP add processes
2025-02-12 proc: fix _thread_set_return destroing mmu scratch mapping
2025-02-12 3D: add case 3D model (FreeCAD + STL)
2025-02-12 kernel: make main naked, it does never return
2025-02-12 proc: use int8_t for generic return value
2025-02-12 lib: add panic()
2025-02-12 syscall: cleanup
2025-02-12 kernel: remove tests
2025-02-12 fat: fix BPB check
2025-02-12 fs: fix mount regression
2025-02-12 lib: add binary heap
2025-02-12 fs: refactor fs_open to allow create op
2025-02-12 lib: add strdup
2025-02-12 mem: fix kmalloc alignment
2025-02-12 kernel: update the year in relevant headers
2025-02-12 proc: restore ability to start the first process
2025-02-12 proc: remove assert that causes annoying sdcc false-positive warn
2025-02-12 hal: add _thread_longjmp
2025-02-12 proc: WIP add process_fork() implementation (not tested yet)
    REGRESION: process_start will not work anymore - had to remove CONTEXT_LAYOUT_USER from the thread_create.
    Plans for vfork has been replaced with fork. vfork is a whole headache of edge-cases that would both tedious to handle correctly and cost code space. fork() on the other hand require memory map to be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
2025-02-12 proc: make scheduler lock non-recursive
2025-02-12 proc: add fork() syscall (WIP)
2025-02-12 hal: optimize _thread_longjmp
2025-02-12 driver: move DMA to shared module from VGA
2025-02-12 proc: add thread and process ending (WIP, not tested)
2025-02-12 lib: enhance id_storage API, add option to iterate over storage
2025-02-12 usr: add simple test user app
2025-02-12 proc: fix _thread_wait return value setting
2025-02-12 kmalloc: detect double free
2025-02-12 proc: working fork()!
2025-02-12 kernel: increase CODE size
2025-02-12 proc: add process_wait
2025-02-12 syscalls: add user pointer setter/getter
2025-02-12 syscall: add waitpid syscall
2025-02-12 kernel: replace printf() with kprintf(), prepare to ditch SDCC printf implementation
2025-02-13 lib: add lightweight kprintf, replace SDCC printf
2025-02-13 syscalls: fix warnings
2025-02-13 syscall: add process_end syscall
2025-02-13 misc: add simple fdd flasher script
2025-02-13 syscall: add usleep syscall
2025-02-13 process: fix zombify not waking up parent
2025-02-14 proc: add thread_join_all
2025-02-14 proc: fix process exit status passing, use int instead of int8_t
    working fork() + waitpid() combo
2025-02-14 proc: use int8_t for thread_yield result consistently
2025-02-14 lib: add unlocked kprintf
2025-02-14 syscall: fix accessing user pointers located on the stack
2025-02-14 syscall: fix discrepancy in waitpid arg list
2025-02-14 proc: fix thread not being removed from id_storage on join
2025-02-16 syscall: working execv()
2025-02-20 proc: start work on file descriptors
2025-02-22 fw: add basic set of file related syscalls
2025-03-21 lib: fix typo
2025-03-21 fs: remove set_attr op
2025-03-21 fs: add devfs WIP
2025-03-31 kernel: base heap size dynamic
    use all memory available after .bss
2025-03-31 zlibc: fix missing include
2025-03-31 fs: make op arg const in fs_mount
2025-03-31 devfs: fix callbacks
2025-03-31 kernel: mount devfs
2025-03-31 dev: add uart driver (WIP)
2025-04-01 usr: remove bye app, replace test with uart echo
2025-04-01 uart: clear errors - fix broken uart on overrun
    fix wrong rd pointer update on fifo overwrite
2025-04-01 kernel: increase code space
2025-04-01 uart: move irq based driver to the kernel devfs
    Use polling for kernel messages for now.
    Remove CPU hogging - add wait/signal on block.
2025-04-02 process: copy parent fd table on fork, close all fds on exit
    change fd table from table of pointers (2 * 16 bytes) to table of descriptors (3 * 16 bytes)
2025-04-02 usr: add init process (WIP)
2025-04-03 init: fix closing stdout by accident when setting up stderr
2025-04-03 hello: replace uart test with stdin/stdout one
2025-04-03 waitpid: return error if process has no children
2025-04-03 process: transplant children and zombies to init on process end
2025-04-03 process: fix mem leak
2025-04-03 thread_join: remove duplicated code
2025-04-03 thread: optimise thread_sleep_relative
2025-04-03 file: optimise file_fd_resolve
2025-04-13 file: optimise file_dup2
2025-04-13 init: pass only basename as argv[0]
2025-04-13 zesh: start work on shell
2025-04-13 git: add .ZEX, .IMG and .LNK to gitignore
2025-04-13 zesh: basic line collection
2025-05-06 Add workaround for SDCC 4.4.0 nonsensical crash
2025-05-06 build: use multiple jobs for building
2025-05-06 lib/panic: Fix incomplete function declaration
2025-06-15 Initial import from ZAK180
2025-06-15 hw: simplify logic, replace some SSI with GALs
2025-06-17 hw: add memory decoder GAL source and .jed
2025-06-17 hw: color text mode VGA (WIP)
2025-06-18 hw: change user port footprint (less offset)
2025-06-19 hw: finish schematic, start routing
2025-06-19 hw: continue routing
2025-06-19 hw: connect VA14 to GND
2025-06-19 hw: add production files
2025-06-20 gal: add AY-3-8912 decoder GAL
2025-06-20 hw: make AY-3-8912 decoder equations more readable
2025-06-20 hw: add pdf schematic
2025-06-20 hw: add missing shload_n connection
2025-06-20 cpld: add vga CPLD implementation (not tested yet)
2025-06-21 Update README - memory, I/O map, some details
2025-06-21 PLD gateware repository cleanup
2025-06-21 vga: simulate and fix CPLD gateware. Add TB
2025-07-02 hw: fix hsync/vsync being connected to wrong pins
2025-07-02 pld/z181md: remove dependency on A13, allow access to whore VRAM
2025-07-02 hw/vga: reduce resistance in DAC to impove image sharpness
2025-07-06 hw: rev B
2025-07-20 Fix wrong D-SUB footprints, rev C
2025-07-27 3d: add case model
2025-07-28 3d: add side skirts to the top of the case
2025-08-02 rev D
    - Fix SUB-D footprints yet again,
    - rotate keyboard connector to remove cable twist,
    - add onboard speaker.
2025-08-04 3d: add auxiliary I/O board to the case
2025-08-14 Rev E: fix MAX232 usage
